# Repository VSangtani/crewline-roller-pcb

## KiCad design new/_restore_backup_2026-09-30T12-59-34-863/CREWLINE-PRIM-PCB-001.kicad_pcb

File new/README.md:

# Crewline primary board, brake and E-stop revision

This folder holds the live KiCad 10 project. The revision label on the board is still V3.1-H1.
The previous revision and its reports are in `../history/`.

## What changed since the previous revision

- J7 grows from 4 to 7 positions and carries the brake lines.
- J10 is new, 7 positions, and carries the E-stop lines.
- J8 is removed. Its arming loop now sits on J3 pins 2 to 5, beside MODE_SEL on pin 1.
- J6 is now the seat sensor connector, 3 positions with one spare.
- J2 and all test points are removed.
- J3, J5, J6, J7 and J10 are Molex Micro-Fit 3.0 single-row vertical through-hole headers.
  J1 (XT60) and J4 (Phoenix MKDS screw terminal block) are unchanged.
- Four relays are new: K_BRAKE_CAT1, K_BRAKE_CAT2, ESTOP_COM_RELAY1 and ESTOP_COM_RELAY2.
  The existing brake relay is now K_BRAKE_SEAT_BOMAG1.
- All relay logic for brake and E-stop sits on the child sheet `brake-estop.kicad_sch`.
- D1, the flyback diode across the POWER1 coil, is turned round so its cathode is on ARMED_HOT.
  The original drawing had it forward-biased across the coil.
- R_ARMED_PD1 is removed. The POWER1 coil already ties ARMED_HOT to ground.
- The six red LEDs use the standard LED symbol, pin 1 cathode, so they match the footprint mark
  and the assembler's library convention.
- The six DNP flags on C1, J1, J9 and the three DPDT relays are cleared. All are fitted.
- Every part number was checked against the JLCPCB parts library. See the BOM section.
- The custom symbols and footprints live in `lib/` and are registered in the project library tables.
- The board is 136 by 132 mm. It grew 56.5 mm to the right for the Phoenix headers, then shrank 21.5 mm after the Molex swap.

## Files

- `CREWLINE-PRIM-PCB-001.kicad_pro`, `.kicad_sch`, `.kicad_pcb` are the project, root sheet and board.
- `brake-estop.kicad_sch` is the child sheet with the relay logic.
- `schematic.pdf` is the two-page schematic export.
- `pcb-top.png` and `pcb-bottom.png` are the native renders.
- `pcb.step` is the native solid model.
- `bom.csv` is the bill of materials, grouped by value, footprint and part number.
- `netlist.xml` is the schematic netlist.
- `erc.json` and `drc.json` are the rule check reports.
- `lib/` holds the project symbol and footprint libraries. `V31_H1.pretty` holds the Phoenix headers
  of the previous revision, kept for reference.
- `models/` holds the 3D models.
- `tools/` holds the grid router and its helpers. See `tools/README.md`.
- `manufacturing/` holds the Gerber set, the drill files and the JLCPCB assembly files. See `manufacturing/README.md`.

## Connectors

| Ref | Function | Part | Mating housing | Fitted by |
|---|---|---|---|---|
| J1 | Battery | Amass XT60PW-M | XT60 plug | JLCPCB |
| J3 | Mode select and arming loop, 5 way | Molex 43650-0515 | 43645-0500 | JLCPCB |
| J4 | Power outputs, 10 way screw terminal | Phoenix MKDS 1,5/10-5,08, 1715802 | none, screw | Customer |
| J5 | CAN cables, 10 way | Molex 43650-1015 | 43645-1000 | JLCPCB |
| J6 | Seat sensor, 3 way | Molex 43650-0315 | 43645-0300 | JLCPCB |
| J7 | Brake, 7 way | Molex 43650-0715 | 43645-0700 | JLCPCB |
| J9 | Converter shield, 2 by 6 pin header | 2.54 mm header | shield | JLCPCB |
| J10 | E-stop, 7 way | Molex 43650-0715 | 43645-0700 | JLCPCB |

J7 and J10 take the same plug. Label both ends of each harness. Harness contacts are the Molex
43030 series, in the 18 to 20 AWG and 20 to 24 AWG versions, crimped with the Molex tool.

### Pin tables

| Pin | J3 | J6 | J7 | J10 |
|---|---|---|---|---|
| 1 | MODE_SEL | ECU_SEAT | BRAKE_JET | ESTOP_JOY_NG |
| 2 | +12V_GATED | SEAT | BRAKE_JOY | ESTOP_JOY |
| 3 | loop, joined to 4 | spare | BRAKE_ECU | ESTOP_ECU |
| 4 | loop, joined to 3 | | BRAKE_JOY_NF | ESTOP_REMOTE |
| 5 | ARMED_HOT | | BRAKE_JOY_NG | ESTOP_ECU_NF |
| 6 | | | BRAKE_ECU_NF | ESTOP_ECU_NF |
| 7 | | | BRAKE_ECU_NG | ESTOP_ECU_NG |

J10 pins 5 and 6 are the same net because ESTOP_JOY_NF is wired directly to ESTOP_ECU_NF.

| Pin | J5 | J4 |
|---|---|---|
| 1 | ECU_CANL | STARLINK_PWR_P |
| 2 | JET2_CANL | GND |
| 3 | JET2_CANH | JET_DIO_PWR_P |
| 4 | ECU_CANH | GND |
| 5 | JOY_CANH | LED_PWR_P |
| 6 | JET1_CANH | GND |
| 7 | JET1_CANH | JETSON_PWR_P |
| 8 | JET1_CANL | GND |
| 9 | JET1_CANL | STEER_PWR_P |
| 10 | JOY_CANL | GND |

J5 pins 6 and 7, and 8 and 9, are doubled so two cables can land on the JET1 bus without a splice.

## Relay coils

Every coil returns through MODE_SEL_DRV, which Q_MODE1 pulls low when MODE_SEL is high.

| Relay | Coil supply | Series diode |
|---|---|---|
| K_BRAKE_SEAT_BOMAG1 | +12V_KIT | none |
| K_BRAKE_CAT1 | +12V_KIT | none |
| K_BRAKE_CAT2 | BRAKE_JET | D_BRAKEJET_SER1 |
| ESTOP_COM_RELAY1 | +12V_KIT | none |
| ESTOP_COM_RELAY2 | ESTOP_REMOTE | D_ESTOPREMOTE_SER1 |

BRAKE_JET and ESTOP_REMOTE come from the Syslogic carrier outputs, which are isolated high-side
switches at 12 V maximum. The series diode blocks any reverse path into them. With MODE_SEL_DRV
floating near 12 V in manual mode, the two coils fed from those outputs see no useful voltage and
stay released. If a later carrier ever drives these lines from 24 V, or from a supply that is live
while the kit is disarmed, return those two coils through a relay contact instead of MODE_SEL_DRV.
Each coil draws about 17 mA and each indicator LED about 5 mA.

## Brake behaviour

| Mode | BRAKE_JET | BRAKE_ECU | BRAKE_ECU_NG | BRAKE_ECU_NF |
|---|---|---|---|---|
| manual | any | BRAKE_JOY | BRAKE_JOY_NG | BRAKE_JOY_NF |
| autonomy | 12 V, released | BRAKE_JET | GND | open |
| autonomy | 0 V, applied, or Jetson dead | BRAKE_JET | open | GND |

## E-stop behaviour

ESTOP_ECU_NF is wired directly to ESTOP_JOY_NF.

| Mode | ESTOP_REMOTE | ESTOP_ECU | ESTOP_ECU_NG | ESTOP_ECU_NF |
|---|---|---|---|---|
| manual | any | ESTOP_JOY | ESTOP_JOY_NG | ESTOP_JOY_NF |
| autonomy | 12 V | ESTOP_JOY | ESTOP_JOY_NG | ESTOP_JOY_NF |
| autonomy | 0 V, or Jetson dead | GND | open | ESTOP_JOY_NF and ESTOP_JOY_NG, tied together |

In the E-stop stop state the NF line takes whatever the joystick NG line carries. It is not
grounded from the board. Confirm that the Bomag input accepts this before the first vehicle test.

## Board layout

- J5, J7 and J10 sit on the bottom edge between the mounting holes. J3 and J6 sit on the left edge.
- The seven DPDT relays sit in one row at Y 143.22 mm. Each has its flyback diode 3 mm above the
  coil pads and its LED and resistor above that.
- The inner layers are the ground plane (In1.Cu) and the +12V_KIT plane (In2.Cu). The front layer
  carries a ground fill in the gaps. Every pad on those nets joins its fill with thermal spokes.
- Track and via sizes follow the net classes: 2.5 mm tracks with 1.0/0.5 mm vias for +12V_GATED,
  1.0 mm tracks with 0.8/0.4 mm vias for +12V_KIT and the power outputs, 0.4 to 0.6 mm tracks with
  0.6/0.3 mm vias for signals.
- No track runs inside a mounting hole washer area or closer than 1.8 mm to the board edge.
- The mounting holes are H1 to H4 on a 120 by 115 mm rectangle: (60, 58), (180, 58), (60, 173)
  and (180, 173) in board coordinates. They are board-only footprints with no schematic symbol.
- The connector swap and the final relay routing were done by hand in the editor. The first routing
  pass used `tools/router.py`.

## BOM

`bom.csv` carries a manufacturer part number, an LCSC number and, where JLCPCB does not fit the
part, an Assembly field reading "Customer fitted". Every LCSC number was opened on the JLCPCB parts
page and checked for package, value, rating, stock and assembly type. Parts fitted by the customer
after assembly:

- J4, Phoenix 1715802, screw terminal block.
- F_MAIN1, F_STEER1, F_JET1, F_CONV1, F_DIO1 and F_LED1, Keystone 3568 blade fuse holders.
  The fuses themselves are not on the BOM: 30 A main, 15 A steering, 10 A Jetson, 10 A converter,
  5 A DIO and 3 A LED.

## Verification

- ERC reports one warning. ESTOP_ECU_NF and ESTOP_JOY_NF name the same net by design.
- DRC reports zero errors, zero warnings and zero unconnected items.
- Every pad net on the board was compared with the schematic netlist. All 245 match.
- The netlist was compared before and after every scripted schematic edit. Only the intended nets
  changed each time.
- An independent review of the schematic, the board and the BOM was run after the first routing.
- These checks are switched off in the project settings and were confirmed clean when switched on:
  ERC single_global_label, four_way_junction and footprint_filter; DRC missing_courtyard and
  footprint_type_mismatch. The track_not_centered_on_via check is switched on.

## Open items before manufacture

- Run Update PCB from Schematic once more so the footprint fields take the audited part numbers.
  Until then the parity check lists 52 field differences.
- Decide whether the six fuse holders stay customer fitted or move to a JLCPCB-stocked holder. A
  replacement must match the Keystone 3568 footprint: two 1.78 mm holes per terminal, 3.4 mm apart,
  with the terminals 9.92 mm apart.
- Bump the revision label before the order and add a revision text on the silkscreen. The schematic
  title blocks are empty.
- Confirm the harness contact and crimp tool part numbers from the Molex site before ordering.
- KiCad's 3D model library has no model for the Micro-Fit 43650 headers, so `pcb.step` and the renders show the five headers as bare pads. Molex offers STEP files for them on the part pages; drop one into `models/` and point the footprint at it if the enclosure fit needs them.

## Open questions for the original board designer

- JOY_TERM_R1 and STEER_TERM_R1 are both 120 ohm across JET1_CANH and JET1_CANL, which puts 60 ohm
  on that bus from this board alone. Both are fitted on the boards in service. A CAN bus normally has
  one 120 ohm terminator at each end and none in the middle. Was this intended, for example because
  the board sits at the end of two separate cable runs?
- D1 on the boards in service: the original drawing had it forward-biased across the POWER1 coil, so
  the fitted part is either reversed relative to the drawing or has failed open.

## Tools

The first routing pass was made with `tools/router.py` under the KiCad Python interpreter. Run the
rule check after every change. The router is not a substitute for it.

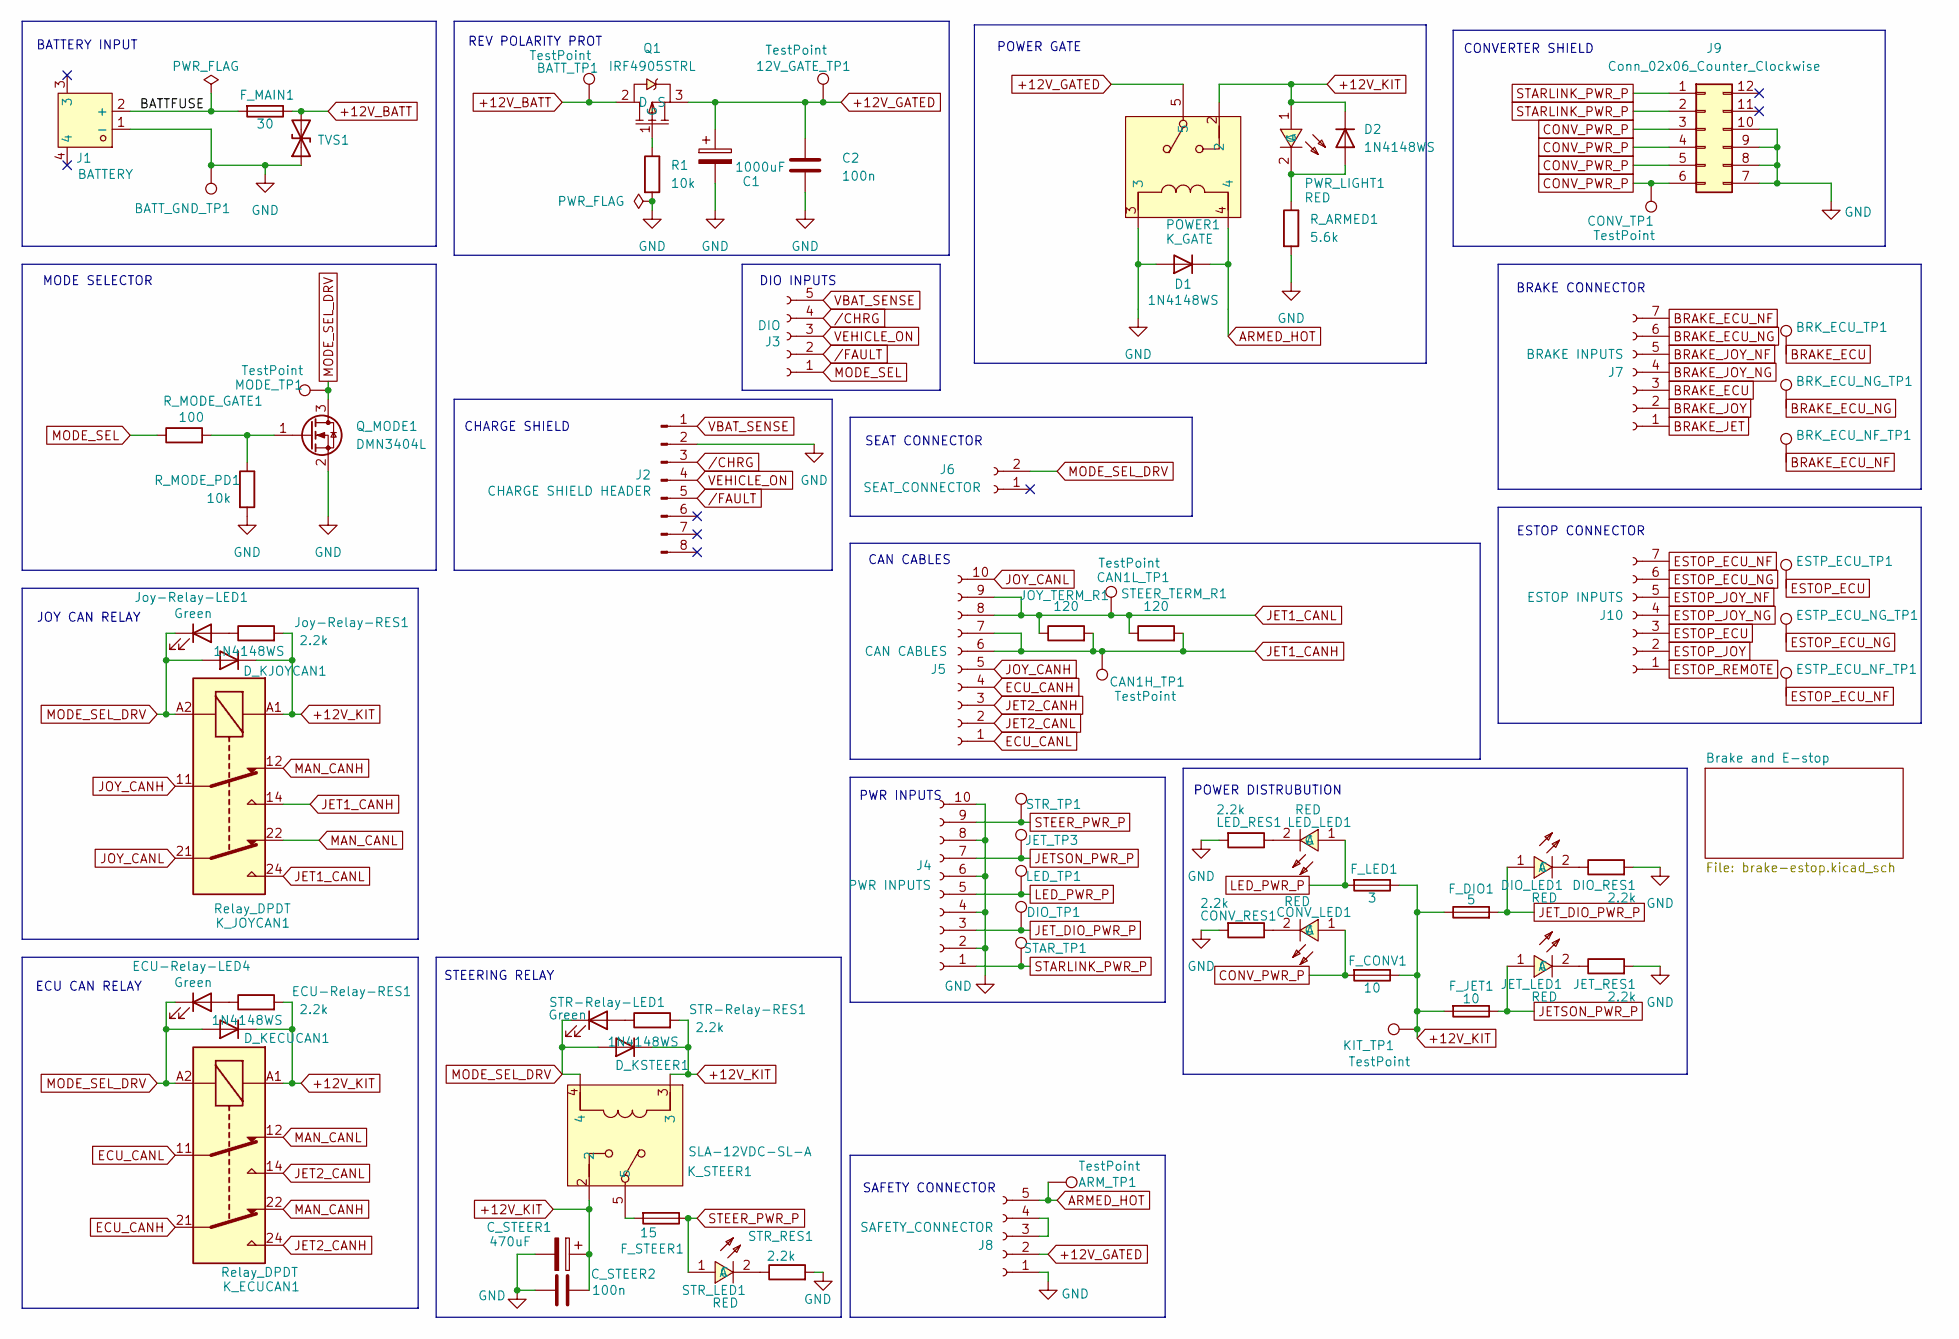
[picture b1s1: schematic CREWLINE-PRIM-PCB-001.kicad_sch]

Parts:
12V_GATE_TP1: TestPoint; TEST-TH_BD2.54-P1.4_RED; LCSC Part C5277086
ARM_TP1: TestPoint; TEST-TH_BD2.54-P1.4_BLACK; LCSC Part C5199801
BATT_GND_TP1: TestPoint; TEST-TH_BD2.54-P1.4_BLACK; LCSC Part C5199801
BATT_TP1: TestPoint; TEST-TH_BD2.54-P1.4_RED; LCSC Part C5277086
BRK_ECU_NF_TP1: TestPoint; TEST-TH_BD2.54-P1.4_BLACK; LCSC Part C5199801
BRK_ECU_NG_TP1: TestPoint; TEST-TH_BD2.54-P1.4_BLACK; LCSC Part C5199801
BRK_ECU_TP1: TestPoint; TEST-TH_BD2.54-P1.4_BLACK; LCSC Part C5199801
C1: 1000uF; ECA1EM102; LCSC Part C44650
C2: 100n; C_0805_2012Metric; LCSC Part C49678
CAN1H_TP1, CAN1L_TP1: TestPoint; TEST-TH_BD2.54-P1.4_BLACK; LCSC Part C5199801
CONV_LED1: RED; LED_0805_2012Metric
CONV_RES1: 2.2k; R_0805_2012Metric; LCSC Part C25879
CONV_TP1: TestPoint; TEST-TH_BD2.54-P1.4_RED; LCSC Part C5277086
C_STEER1: 470uF; C_Radial_D8.0mm_H11.5mm_P3.50mm; LCSC Part C44897
C_STEER2: 100n; C_0805_2012Metric; LCSC Part C49678
D1, D2: 1N4148WS; SOD-323_L1.8-W1.3-LS2.5-RD; LCSC Part C81598
DIO_LED1: RED; LED_0805_2012Metric
DIO_RES1: 2.2k; R_0805_2012Metric; LCSC Part C25879
DIO_TP1: TestPoint; TEST-TH_BD2.54-P1.4_RED; LCSC Part C5277086
D_KECUCAN1: 1N4148WS; SOD-323_L1.8-W1.3-LS2.5-RD; LCSC Part C81598
D_KJOYCAN1: 1N4148WS; SOD-323_L1.8-W1.3-LS2.5-RD; LCSC Part C81598
D_KSTEER1: 1N4148WS; SOD-323_L1.8-W1.3-LS2.5-RD; LCSC Part C81598
ECU-Relay-LED4: Green; LED_0805_2012Metric; LCSC Part C72043
ECU-Relay-RES1: 2.2k; R_0805_2012Metric; LCSC Part C25879
ESTP_ECU_NF_TP1: TestPoint; TEST-TH_BD2.54-P1.4_BLACK; LCSC Part C5199801
ESTP_ECU_NG_TP1: TestPoint; TEST-TH_BD2.54-P1.4_BLACK; LCSC Part C5199801
ESTP_ECU_TP1: TestPoint; TEST-TH_BD2.54-P1.4_BLACK; LCSC Part C5199801
F_CONV1: 10; Fuseholder_Blade_Mini_Keystone_3568; LCSC Part DNP
F_DIO1: 5; Fuseholder_Blade_Mini_Keystone_3568; LCSC Part DNP
F_JET1: 10; Fuseholder_Blade_Mini_Keystone_3568; LCSC Part DNP
F_LED1: 3; Fuseholder_Blade_Mini_Keystone_3568; LCSC Part DNP
F_MAIN1: 30; Fuseholder_Blade_Mini_Keystone_3568; MPN 0297030.U; LCSC Part DNP
F_STEER1: 15; Fuseholder_Blade_Mini_Keystone_3568; LCSC Part DNP
J1: BATTERY; CONN-TH_XT60PW-M; MPN XT60PW-M; LCSC Part C98732
J2: CHARGE SHIELD HEADER; PinSocket_2x04_P2.54mm_Vertical; LCSC Part DNP
J3: DIO; MCV_1.5_5_5.08_Pad2.6; MPN 1836325
J4: PWR INPUTS; TerminalBlock_Phoenix_MKDS-1,5-10-5.08_1x10_P5.08mm_Horizon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; LCSC Part DNP
J5: CAN CABLES; MCV_1.5_10_5.08_Pad2.6; MPN 1836370
J6: SEAT_CONNECTOR; WAGO_2604-1102; LCSC Part DNP
J7: BRAKE INPUTS; MCV_1.5_7_5.08_Pad2.6; MPN 1836341
J8: SAFETY_CONNECTOR; MCV_1.5_5_5.08_Pad2.6; MPN 1836325
J9: Conn_02x06_Counter_Clockwise; PinHeader_2x06_P2.54mm_Vertical; LCSC Part C124388
J10: ESTOP INPUTS; MCV_1.5_7_5.08_Pad2.6; MPN 1836341
JET_LED1: RED; LED_0805_2012Metric
JET_RES1: 2.2k; R_0805_2012Metric; LCSC Part C25879
JET_TP3: TestPoint; TEST-TH_BD2.54-P1.4_RED; LCSC Part C5277086
JOY_TERM_R1: 120; R_0805_2012Metric; LCSC Part C22787
Joy-Relay-LED1: Green; LED_0805_2012Metric; LCSC Part C72043
Joy-Relay-RES1: 2.2k; R_0805_2012Metric; LCSC Part C25879
KIT_TP1: TestPoint; TEST-TH_BD2.54-P1.4_RED; LCSC Part C5277086
K_ECUCAN1: Relay_DPDT; Relay_DPDT_Omron_G6A; LCSC Part C45404
K_JOYCAN1: Relay_DPDT; Relay_DPDT_Omron_G6A; LCSC Part C45404
K_STEER1: SLA-12VDC-SL-A; RELAY-TH_SLA-XXVDC-XL-A; MPN SLA-12VDC-SL-A; LCSC Part C55194
LED_LED1: RED; LED_0805_2012Metric
LED_RES1: 2.2k; R_0805_2012Metric; LCSC Part C25879
LED_TP1: TestPoint; TEST-TH_BD2.54-P1.4_RED; LCSC Part C5277086
MODE_TP1: TestPoint; TEST-TH_BD2.54-P1.4_BLACK; LCSC Part C5199801
POWER1: K_GATE; RELAY-TH_SLA-XXVDC-XL-A; MPN SLA-12VDC-SL-A; LCSC Part C55194
PWR_LIGHT1: RED; LED_0805_2012Metric
Q1: IRF4905STRL; TO-252-2_L6.6-W6.1-P4.57-LS10.1-BR-CW; MPN IRF4905STRL(UMW); LCSC Part C7471852
Q_MODE1: DMN3404L; SOT-23; LCSC Part C700958
R1: 10k; R_0805_2012Metric; LCSC Part C17414
R_ARMED1: 5.6k; R_0805_2012Metric; LCSC Part C17475
R_MODE_GATE1: 100; R_0805_2012Metric; LCSC Part C17561
R_MODE_PD1: 10k; R_0805_2012Metric; LCSC Part C17414
STAR_TP1: TestPoint; TEST-TH_BD2.54-P1.4_RED; LCSC Part C5277086
STEER_TERM_R1: 120; R_0805_2012Metric; LCSC Part C22787
STR-Relay-LED1: Green; LED_0805_2012Metric; LCSC Part C72043
STR-Relay-RES1: 2.2k; R_0805_2012Metric; LCSC Part C25879
STR_LED1: RED; LED_0805_2012Metric
STR_RES1: 2.2k; R_0805_2012Metric; LCSC Part C25879
STR_TP1: TestPoint; TEST-TH_BD2.54-P1.4_RED; LCSC Part C5277086
TVS1: SMBJ24CA; D_SMB; MPN SMBJ24CA-13-F; LCSC Part C13616

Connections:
+12V_BATT: BATT_TP1.1 (1_1), F_MAIN1.1, Q1.2 (D), TVS1.2 (A2)
+12V_GATED: 12V_GATE_TP1.1 (1_1), C1.1, C2.1, J8.2, POWER1.5, Q1.3 (S)
+12V_KIT: C_STEER1.1, C_STEER2.2, D2.1 (K), D_KECUCAN1.1 (K), D_KJOYCAN1.1 (K), D_KSTEER1.1 (K), ECU-Relay-RES1.2, F_CONV1.1, F_DIO1.1, F_JET1.2, F_LED1.1, Joy-Relay-RES1.2, KIT_TP1.1 (1_1), K_ECUCAN1.A1, K_JOYCAN1.A1, K_STEER1.2, K_STEER1.3, POWER1.2, PWR_LIGHT1.1 (A), STR-Relay-RES1.2; also elsewhere on the board
/BATTFUSE: F_MAIN1.2, J1.2 (+)
ARMED_HOT: ARM_TP1.1 (1_1), D1.1 (K), J8.5, POWER1.4
BRAKE_ECU: BRK_ECU_TP1.1 (1_1), J7.3; also elsewhere on the board
BRAKE_ECU_NF: BRK_ECU_NF_TP1.1 (1_1), J7.7; also elsewhere on the board
BRAKE_ECU_NG: BRK_ECU_NG_TP1.1 (1_1), J7.6; also elsewhere on the board
BRAKE_JET: J7.1; also elsewhere on the board
BRAKE_JOY: J7.2; also elsewhere on the board
BRAKE_JOY_NF: J7.5; also elsewhere on the board
BRAKE_JOY_NG: J7.4; also elsewhere on the board
CONV_PWR_P: CONV_LED1.1 (A), CONV_TP1.1 (1_1), F_CONV1.2, J9.3, J9.4, J9.5, J9.6
ECU_CANH: J5.4, K_ECUCAN1.21
ECU_CANL: J5.1, K_ECUCAN1.11
ESTOP_ECU: ESTP_ECU_TP1.1 (1_1), J10.3; also elsewhere on the board
ESTOP_ECU_NF: ESTP_ECU_NF_TP1.1 (1_1), J10.5, J10.7; also elsewhere on the board
ESTOP_ECU_NG: ESTP_ECU_NG_TP1.1 (1_1), J10.6; also elsewhere on the board
ESTOP_JOY: J10.2; also elsewhere on the board
ESTOP_JOY_NG: J10.4; also elsewhere on the board
ESTOP_REMOTE: J10.1; also elsewhere on the board
GND: BATT_GND_TP1.1 (1_1), C1.2, C2.2, CONV_RES1.2, C_STEER1.2, C_STEER2.1, D1.2 (A), DIO_RES1.2, J1.1 (-), J2.2, J4.2, J4.4, J4.6, J4.8, J4.10, J8.1, J9.7, J9.8, J9.9, J9.10, JET_RES1.2, LED_RES1.2, POWER1.3, Q_MODE1.2 (S), R1.2, R_ARMED1.2, R_MODE_PD1.2, STR_RES1.2, TVS1.1 (A1); also elsewhere on the board
JET1_CANH: CAN1H_TP1.1 (1_1), J5.6, J5.7, JOY_TERM_R1.2, K_JOYCAN1.14, STEER_TERM_R1.2
JET1_CANL: CAN1L_TP1.1 (1_1), J5.8, J5.9, JOY_TERM_R1.1, K_JOYCAN1.24, STEER_TERM_R1.1
JET2_CANH: J5.3, K_ECUCAN1.24
JET2_CANL: J5.2, K_ECUCAN1.14
JETSON_PWR_P: F_JET1.1, J4.7, JET_LED1.1 (A), JET_TP3.1 (1_1)
JET_DIO_PWR_P: DIO_LED1.1 (A), DIO_TP1.1 (1_1), F_DIO1.2, J4.3
JOY_CANH: J5.5, K_JOYCAN1.11
JOY_CANL: J5.10, K_JOYCAN1.21
LED_PWR_P: F_LED1.2, J4.5, LED_LED1.1 (A), LED_TP1.1 (1_1)
MAN_CANH: K_ECUCAN1.22, K_JOYCAN1.12
MAN_CANL: K_ECUCAN1.12, K_JOYCAN1.22
MODE_SEL: J3.1, R_MODE_GATE1.1
MODE_SEL_DRV: D_KECUCAN1.2 (A), D_KJOYCAN1.2 (A), D_KSTEER1.2 (A), ECU-Relay-LED4.1 (K), J6.2 (Pin_2_2), Joy-Relay-LED1.1 (K), K_ECUCAN1.A2, K_JOYCAN1.A2, K_STEER1.4, MODE_TP1.1 (1_1), Q_MODE1.3 (D), STR-Relay-LED1.1 (K); also elsewhere on the board
unnamed: CONV_LED1.2 (C), CONV_RES1.1
unnamed: D2.2 (A), PWR_LIGHT1.2 (C), R_ARMED1.1
unnamed: DIO_LED1.2 (C), DIO_RES1.1
unnamed: ECU-Relay-LED4.2 (A), ECU-Relay-RES1.1
unnamed: F_STEER1.2, K_STEER1.5
unnamed: J8.3, J8.4
unnamed: JET_LED1.2 (C), JET_RES1.1
unnamed: Joy-Relay-LED1.2 (A), Joy-Relay-RES1.1
unnamed: LED_LED1.2 (C), LED_RES1.1
unnamed: Q1.1 (G), R1.1
unnamed: Q_MODE1.1 (G), R_MODE_GATE1.2, R_MODE_PD1.1
unnamed: STR-Relay-LED1.2 (A), STR-Relay-RES1.1
unnamed: STR_LED1.2 (C), STR_RES1.1
STARLINK_PWR_P: J4.1, J9.1, J9.2, STAR_TP1.1 (1_1)
STEER_PWR_P: F_STEER1.1, J4.9, STR_LED1.1 (A), STR_TP1.1 (1_1)
VBAT_SENSE: J2.1, J3.5
VEHICLE_ON: J2.4, J3.3
/CHRG: J2.3, J3.4
/FAULT: J2.5, J3.2

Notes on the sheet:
SAFETY CONNECTOR
CHARGE SHIELD
CONVERTER SHIELD
DIO INPUTS
STEERING RELAY
POWER GATE
SEAT CONNECTOR
MODE SELECTOR
POWER DISTRUBUTION
REV POLARITY PROT
ECU CAN RELAY
PWR INPUTS
BATTERY INPUT
JOY CAN RELAY
CAN CABLES
BRAKE CONNECTOR
ESTOP CONNECTOR

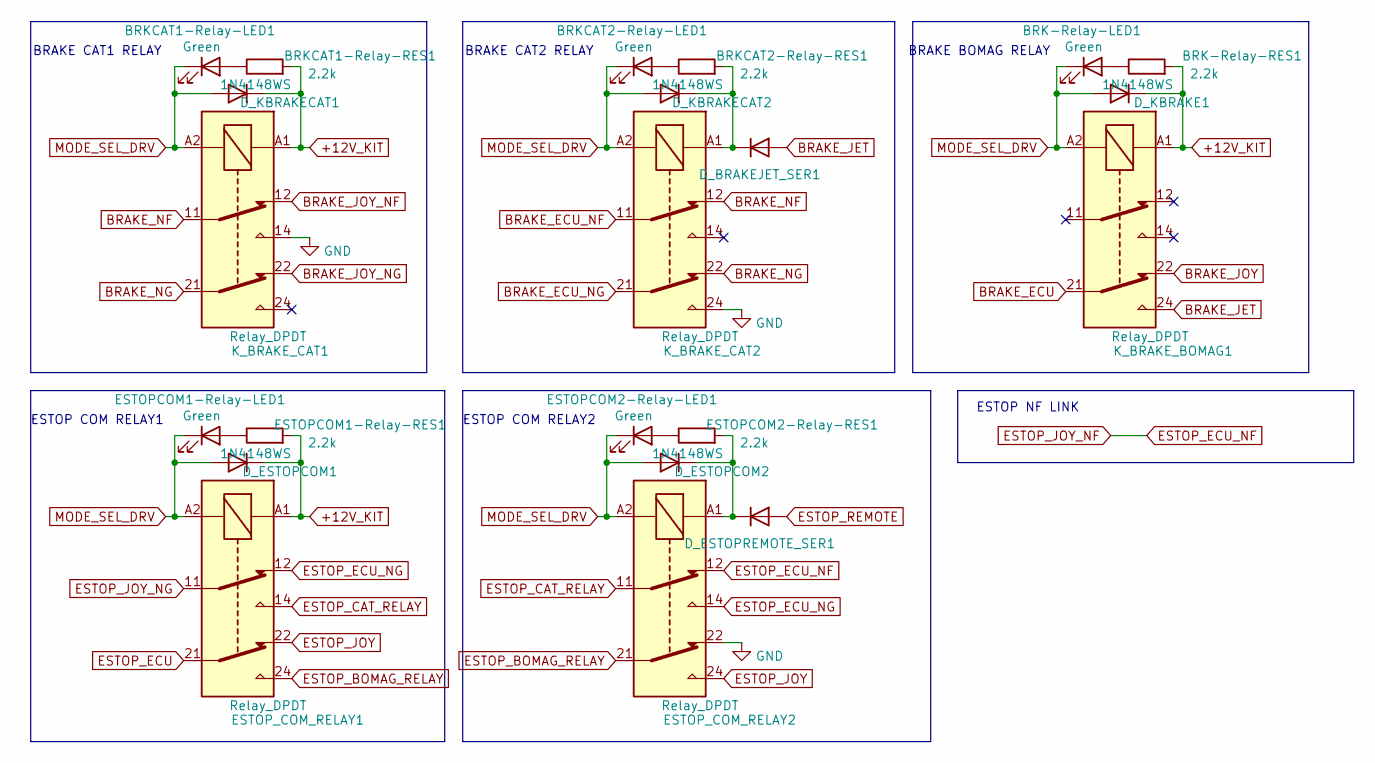
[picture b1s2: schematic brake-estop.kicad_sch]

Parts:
BRK-Relay-LED1: Green; LED_0805_2012Metric; LCSC Part C72043
BRK-Relay-RES1: 2.2k; R_0805_2012Metric; LCSC Part C25879
BRKCAT1-Relay-LED1, BRKCAT2-Relay-LED1: Green; LED_0805_2012Metric; LCSC Part C72043
BRKCAT1-Relay-RES1, BRKCAT2-Relay-RES1: 2.2k; R_0805_2012Metric; LCSC Part C25879
D_BRAKEJET_SER1: 1N4148WS; SOD-323_L1.8-W1.3-LS2.5-RD; LCSC Part C81598
D_ESTOPCOM1, D_ESTOPCOM2: 1N4148WS; SOD-323_L1.8-W1.3-LS2.5-RD; LCSC Part C81598
D_ESTOPREMOTE_SER1: 1N4148WS; SOD-323_L1.8-W1.3-LS2.5-RD; LCSC Part C81598
D_KBRAKE1: 1N4148WS; SOD-323_L1.8-W1.3-LS2.5-RD; LCSC Part C81598
D_KBRAKECAT1, D_KBRAKECAT2: 1N4148WS; SOD-323_L1.8-W1.3-LS2.5-RD; LCSC Part C81598
ESTOPCOM1-Relay-LED1, ESTOPCOM2-Relay-LED1: Green; LED_0805_2012Metric; LCSC Part C72043
ESTOPCOM1-Relay-RES1, ESTOPCOM2-Relay-RES1: 2.2k; R_0805_2012Metric; LCSC Part C25879
ESTOP_COM_RELAY1, ESTOP_COM_RELAY2: Relay_DPDT; Relay_DPDT_Omron_G6A; LCSC Part C45404
K_BRAKE_BOMAG1: Relay_DPDT; Relay_DPDT_Omron_G6A; LCSC Part C45404
K_BRAKE_CAT1, K_BRAKE_CAT2: Relay_DPDT; Relay_DPDT_Omron_G6A; LCSC Part C45404

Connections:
+12V_KIT: BRK-Relay-RES1.2, BRKCAT1-Relay-RES1.2, D_ESTOPCOM1.1 (K), D_KBRAKE1.1 (K), D_KBRAKECAT1.1 (K), ESTOPCOM1-Relay-RES1.2, ESTOP_COM_RELAY1.A1, K_BRAKE_BOMAG1.A1, K_BRAKE_CAT1.A1; also elsewhere on the board
BRAKE_ECU: K_BRAKE_BOMAG1.21; also elsewhere on the board
BRAKE_ECU_NF: K_BRAKE_CAT2.11; also elsewhere on the board
BRAKE_ECU_NG: K_BRAKE_CAT2.21; also elsewhere on the board
BRAKE_JET: D_BRAKEJET_SER1.2 (A), K_BRAKE_BOMAG1.24; also elsewhere on the board
BRAKE_JOY: K_BRAKE_BOMAG1.22; also elsewhere on the board
BRAKE_JOY_NF: K_BRAKE_CAT1.12; also elsewhere on the board
BRAKE_JOY_NG: K_BRAKE_CAT1.22; also elsewhere on the board
BRAKE_NF: K_BRAKE_CAT1.11, K_BRAKE_CAT2.12
BRAKE_NG: K_BRAKE_CAT1.21, K_BRAKE_CAT2.22
ESTOP_BOMAG_RELAY: ESTOP_COM_RELAY1.24, ESTOP_COM_RELAY2.21
ESTOP_CAT_RELAY: ESTOP_COM_RELAY1.14, ESTOP_COM_RELAY2.11
ESTOP_ECU: ESTOP_COM_RELAY1.21; also elsewhere on the board
ESTOP_ECU_NF: ESTOP_COM_RELAY2.12; also elsewhere on the board
ESTOP_ECU_NG: ESTOP_COM_RELAY1.12, ESTOP_COM_RELAY2.14; also elsewhere on the board
ESTOP_JOY: ESTOP_COM_RELAY1.22, ESTOP_COM_RELAY2.24; also elsewhere on the board
ESTOP_JOY_NG: ESTOP_COM_RELAY1.11; also elsewhere on the board
ESTOP_REMOTE: D_ESTOPREMOTE_SER1.2 (A); also elsewhere on the board
GND: ESTOP_COM_RELAY2.22, K_BRAKE_CAT1.14, K_BRAKE_CAT2.24; also elsewhere on the board
MODE_SEL_DRV: BRK-Relay-LED1.1 (K), BRKCAT1-Relay-LED1.1 (K), BRKCAT2-Relay-LED1.1 (K), D_ESTOPCOM1.2 (A), D_ESTOPCOM2.2 (A), D_KBRAKE1.2 (A), D_KBRAKECAT1.2 (A), D_KBRAKECAT2.2 (A), ESTOPCOM1-Relay-LED1.1 (K), ESTOPCOM2-Relay-LED1.1 (K), ESTOP_COM_RELAY1.A2, ESTOP_COM_RELAY2.A2, K_BRAKE_BOMAG1.A2, K_BRAKE_CAT1.A2, K_BRAKE_CAT2.A2; also elsewhere on the board
unnamed: BRK-Relay-LED1.2 (A), BRK-Relay-RES1.1
unnamed: BRKCAT1-Relay-LED1.2 (A), BRKCAT1-Relay-RES1.1
unnamed: BRKCAT2-Relay-LED1.2 (A), BRKCAT2-Relay-RES1.1
unnamed: BRKCAT2-Relay-RES1.2, D_BRAKEJET_SER1.1 (K), D_KBRAKECAT2.1 (K), K_BRAKE_CAT2.A1
unnamed: D_ESTOPCOM2.1 (K), D_ESTOPREMOTE_SER1.1 (K), ESTOPCOM2-Relay-RES1.2, ESTOP_COM_RELAY2.A1
unnamed: ESTOPCOM1-Relay-LED1.2 (A), ESTOPCOM1-Relay-RES1.1
unnamed: ESTOPCOM2-Relay-LED1.2 (A), ESTOPCOM2-Relay-RES1.1

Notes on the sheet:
BRAKE CAT1 RELAY
BRAKE CAT2 RELAY
BRAKE BOMAG RELAY
ESTOP COM RELAY1
ESTOP COM RELAY2
ESTOP NF LINK

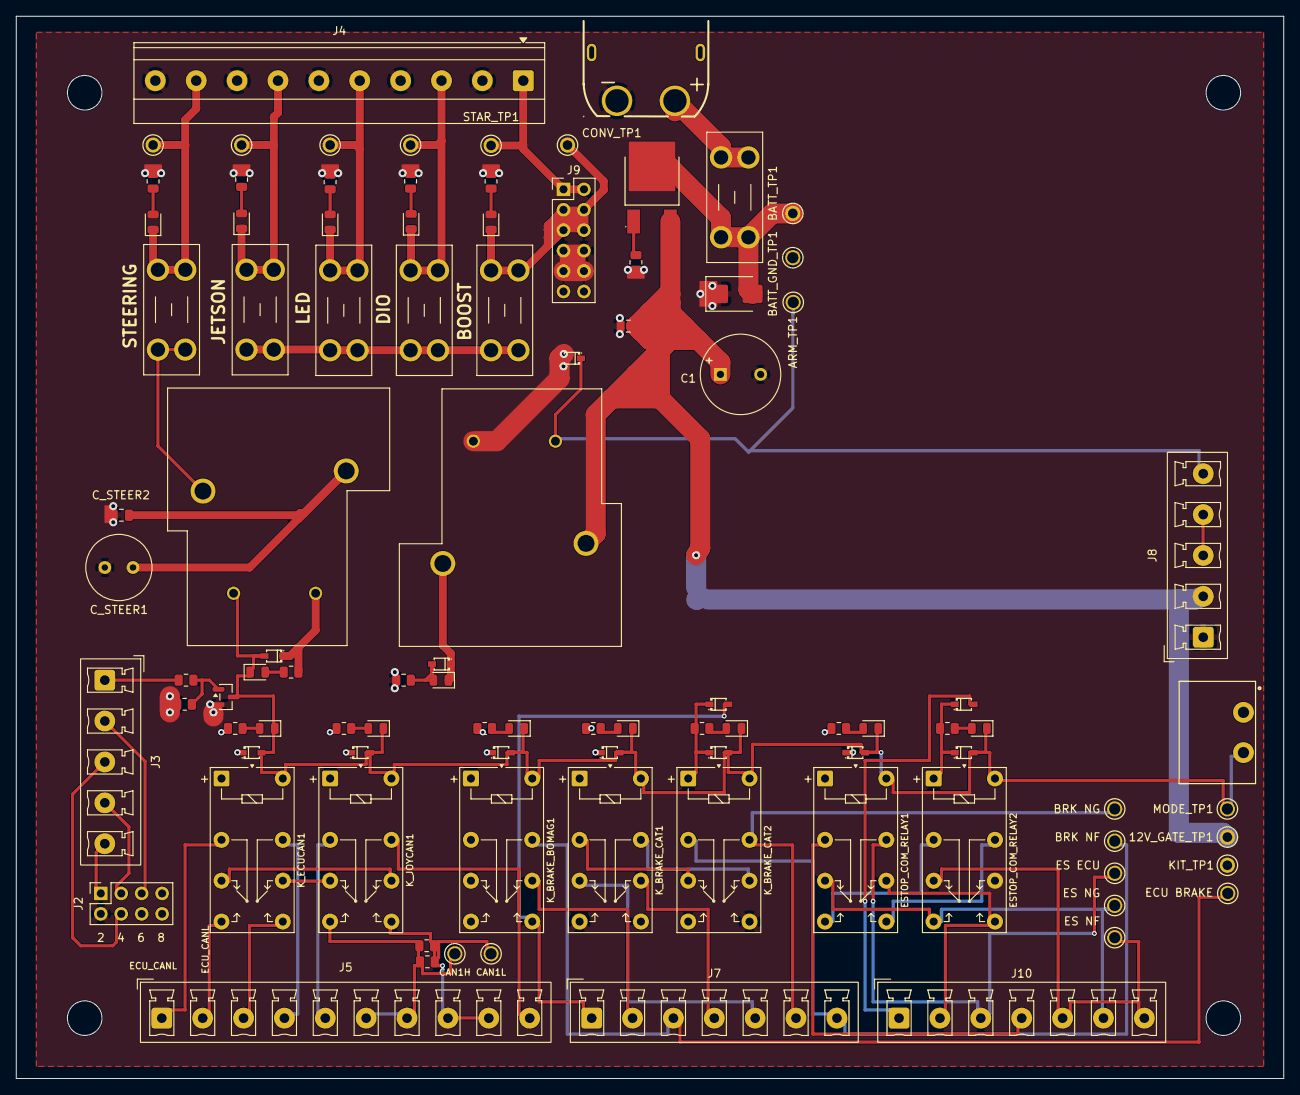
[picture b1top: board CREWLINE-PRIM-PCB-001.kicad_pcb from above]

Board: 4 copper layers, 157.5 x 132.0 mm, 101 parts (0 on the bottom side), 65 nets.

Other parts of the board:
H1, H2, H3, H4: MountingHole_4.3mm_M4
